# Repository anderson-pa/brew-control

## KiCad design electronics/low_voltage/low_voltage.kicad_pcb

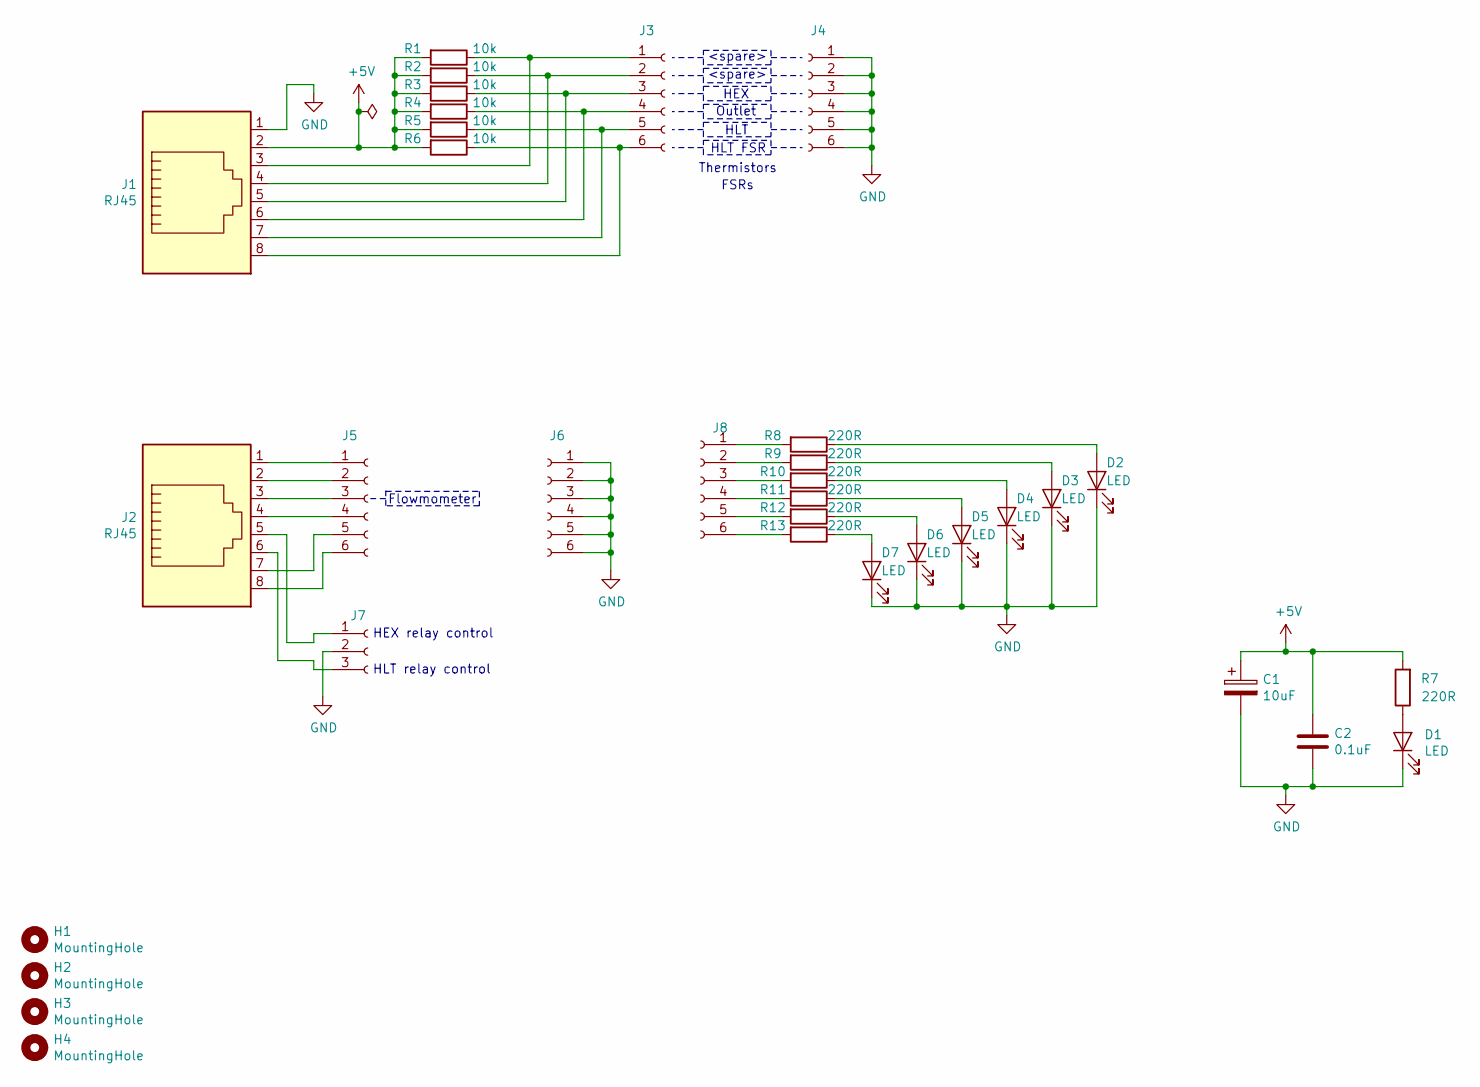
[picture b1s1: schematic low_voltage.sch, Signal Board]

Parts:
C1: 10uF; CP_Radial_D5.0mm_P2.00mm
C2: 0.1uF; C_Disc_D3.8mm_W2.6mm_P2.50mm
D1, D2, D3, D4, D5, D6, D7: LED; LED_D5.0mm
H1, H2, H3, H4: MountingHole; MountingHole_3mm
J1, J2: RJ45; RJ45_Amphenol_54602-x08_Horizontal
J3, J4, J5, J6: Conn_01x06_Female; SPRINGTERMINAL_PRT-08077_2.54MM-6
J7: Conn_01x03_Female; SPRINGTERMINAL_PRT-08074_2.54MM-3
J8: Conn_01x06_Female; PinSocket_1x06_P2.54mm_Vertical
R1, R2, R3, R4, R5, R6: 10k; R_Axial_DIN0207_L6.3mm_D2.5mm_P7.62mm_Horizontal
R7, R8, R9, R10, R11, R12, R13: 220R; R_Axial_DIN0207_L6.3mm_D2.5mm_P7.62mm_Horizontal

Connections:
+5V: C1.1, C2.1, J1.2, R1.2, R2.2, R3.2, R4.2, R5.2, R6.2, R7.2
GND: C1.2, C2.2, D1.1 (K), D2.1 (K), D3.1 (K), D4.1 (K), D5.1 (K), D6.1 (K), D7.1 (K), J1.1, J4.1, J4.2, J4.3, J4.4, J4.5, J4.6, J6.1, J6.2, J6.3, J6.4, J6.5, J6.6, J7.2
unnamed: D1.2 (A), R7.1
unnamed: D2.2 (A), R8.1
unnamed: D3.2 (A), R9.1
unnamed: D4.2 (A), R10.1
unnamed: D5.2 (A), R11.1
unnamed: D6.2 (A), R12.1
unnamed: D7.2 (A), R13.1
unnamed: J1.3, J3.1, R1.1
unnamed: J1.4, J3.2, R2.1
unnamed: J1.5, J3.3, R3.1
unnamed: J1.6, J3.4, R4.1
unnamed: J1.7, J3.5, R5.1
unnamed: J1.8, J3.6, R6.1
unnamed: J2.1, J5.1
unnamed: J2.2, J5.2
unnamed: J2.3, J5.3
unnamed: J2.4, J5.4
unnamed: J2.5, J7.1
unnamed: J2.6, J7.3
unnamed: J2.7, J5.5
unnamed: J2.8, J5.6
unnamed: J8.1, R8.2
unnamed: J8.2, R9.2
unnamed: J8.3, R10.2
unnamed: J8.4, R11.2
unnamed: J8.5, R12.2
unnamed: J8.6, R13.2

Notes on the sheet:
Thermistors
HEX
HLT
Outlet
<spare>
HLT FSR
FSRs
HEX relay control
HLT relay control
Flowmometer

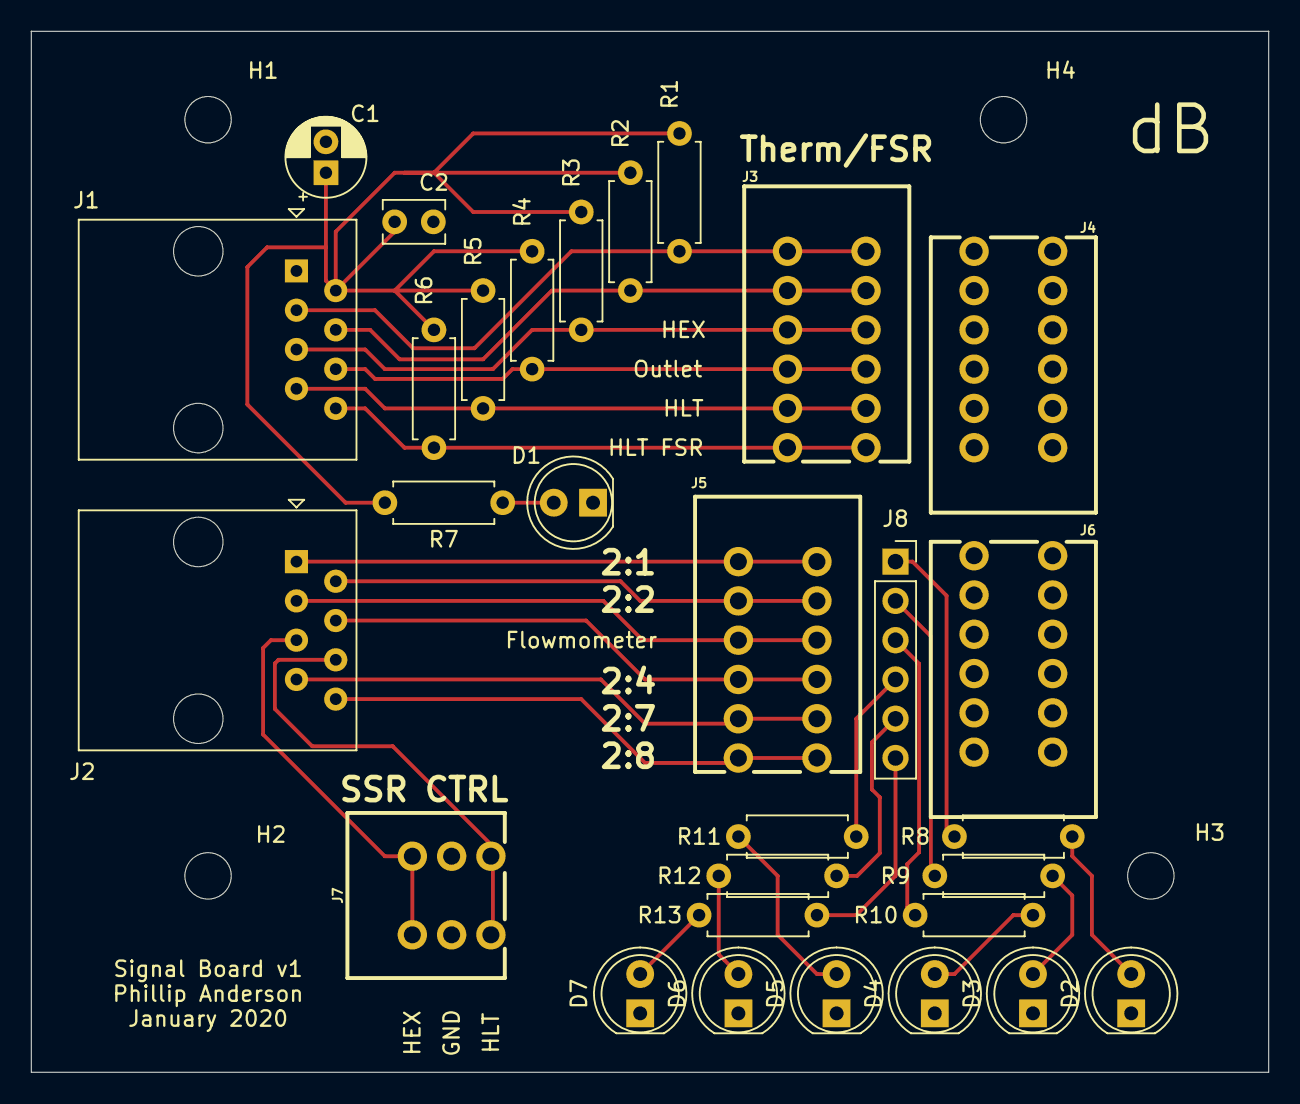
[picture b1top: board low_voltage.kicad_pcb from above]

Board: 2 copper layers, 80.0 x 67.3 mm, 34 parts (0 on the bottom side), 29 nets.

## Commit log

2021-06-15 Add circuit schematics.
